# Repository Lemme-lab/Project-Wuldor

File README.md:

# Project Wuldor
---
## A completely custom 6 Axis Roboter-Arm (Still in progress) that won the 2022 HTL Mössingerstraße Technicus Award. 
---

---

---

---

---

---

---

---

---

## Features 
- Self Designed Stepper Motor Controller (A4988) 
- Self designed Main Controller with a small footprint
- Compact Size Factor
- Esthetic 
- Many other little Features

---

---

---

## Planned Code:
### General:  
A few bullet points and explanations for the code part. Different technologies and programming languages such as C++, WEB-Dev, and Flutter will be used. It will go from Basic C and register manipulation to UI-Development on Cross-Platform Mobile Apps.  
  
- Controlling Axis 1- 5  
- Save Control sequence  
- Remote  Connection  
- Desktop  Application  
- Website  
- Mobile App  
- PHP Database  
- C++, HTML, CSS, JS, FLUTTER, JAVA, Python
- Tensorflow, Keras

---
  
### Website:  
An HTML Website that must be functional and appealing to use. Features will be send via a ESP32 and the included Wireless module. Cross-platform Data will mean that we will have to save the current data and inputs on a small database. UI and other Features will mean that we have to use JS with or without an additional framework.  
 --- 

 --- 
- Checking Power Status  
- Check Wireless Connection  
- Current Voltage/Power Levels  
- Slider  Controlls for Motors  
- Test Motor func  
- Switch Mode (Normal Control, Train ,AI)  
- Cam Live Stream implementation  
- Stop/Start/hold -->pan> Slide buttons  
- Speed  
- Axis coordinates  
  
--- 
  
### Desktop Client  
A C++ or Java desktop client to be used when wired up to the robot arm. From the User ready interface to debbuging, testing and programming features will be included. This is one of the most important interface to the robot arm and as such it will be programmed first.  
  
- Checking Power Status  
- Check Wireless Connection  
- Current Voltage/Power Levels  
- Slider  Controlls for Motors  
- Test Motor func  
- Switch Mode (Normal Control,AI)  
- Cam  
- Debug Features / Console  
- Test  Features  
- Stop/Start/Hold -->  slidebuttons  
- Speed  
  
--- 
  
### Mobile Client  
Last we will do a Mobile Client app for controlling and checking the robot arm on the go. It will be programmed in Flutter or another Mobile Cross Platform Developer Kit.
--- 
  
---   
- Checking Power Status  
- Check Wireless Connection  
- Current-Voltage/Power Levels  
- Settings  
- Live Cam   

---

### Self-Test
Testclasses to exclude code-mistakes. Motors are working in the corract way and also the remote connection and controlling from the web applicatio, if so then we can put everything together and test the whole thing

- Motor
- Remote Connection
- Connections Seriell/Connectors 
  
---
### Currently in Work
---

---
The whole code will be versioned via GIT, inputs to the Roboter Arm tested, and the whole project will be publicly available on GitHub.
---
https://trello.com/b/jWCULnX8
---

## Stepper Motor + Reducer

---

---

------

## Stepper Motor Controller 

------

------

------

------

## Main Controller

------

------

------

------

## Roboter-Arm
---

---

---

---

---

---

------

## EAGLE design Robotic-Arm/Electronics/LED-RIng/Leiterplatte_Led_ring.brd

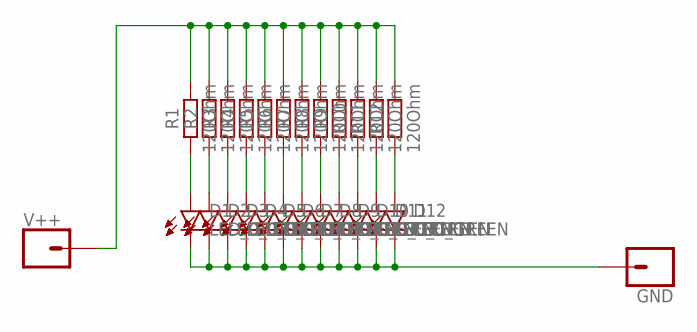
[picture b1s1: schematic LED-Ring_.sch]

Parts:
D1, D2, D3, D4, D5, D6, D7, D8, D9, D10, D11, D12: LED_GREEN; LEDC2012X105N_RND-R
GND: CONN_01PTH_2MM; 1X01_2MM
R1, R2, R3, R4, R5, R6, R7, R8, R9, R10, R11, R12: 120Ohm; RESC3216X70
V++: CONN_01PTH_2MM; 1X01_2MM

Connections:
unnamed: R1.2, R2.2, R3.2, R4.2, R5.2, R6.2, R7.2, R8.2, R9.2, R10.2, R11.2, R12.2, V++.1
unnamed: D1.A, R1.1
unnamed: D2.A, R2.1
unnamed: D3.A, R3.1
unnamed: D4.A, R4.1
unnamed: D5.A, R5.1
unnamed: D6.A, R6.1
unnamed: D7.A, R7.1
unnamed: D8.A, R8.1
unnamed: D9.A, R9.1
unnamed: D10.A, R10.1
unnamed: D11.A, R11.1
unnamed: D12.A, R12.1
unnamed: D1.C, D2.C, D3.C, D4.C, D5.C, D6.C, D7.C, D8.C, D9.C, D10.C, D11.C, D12.C, GND.1

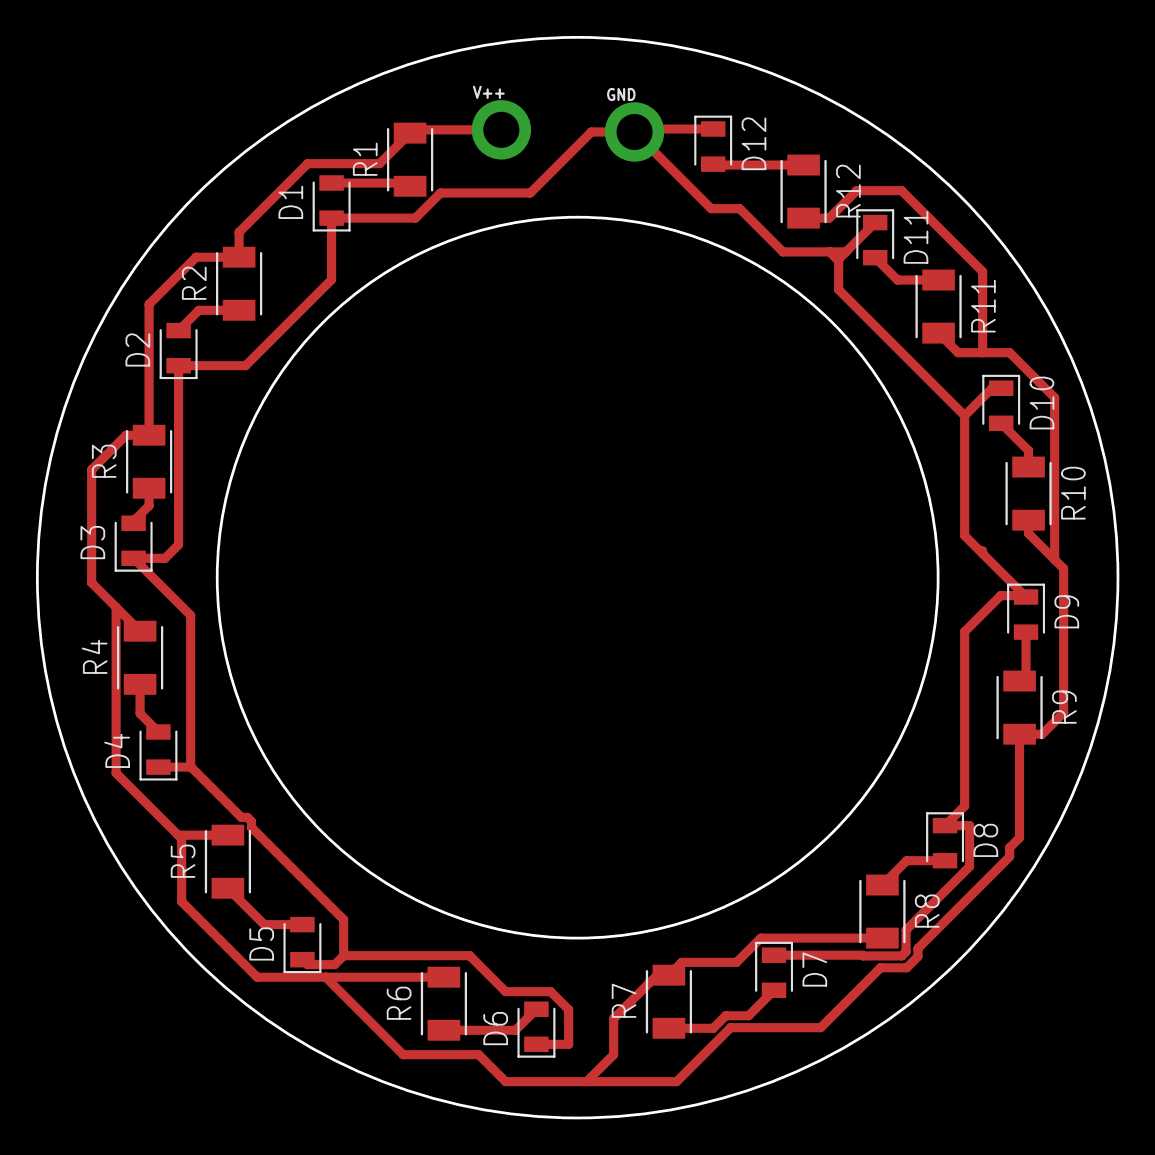
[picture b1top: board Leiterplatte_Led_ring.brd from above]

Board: 2 copper layers, 60.0 x 60.0 mm, 26 parts (0 on the bottom side), 14 nets.

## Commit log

2021-11-14 init
2022-01-16 Added Main Controller to Github
2022-01-16 Added Stepper Controller to Github
2022-01-21 Created and added 17HS15-1684S-HG100 100:1 Ratio High Torgue Stepper motor
2022-01-21 updatet 17HS4401
2022-01-21 Updatet Roboter Arm Combined
2022-01-21 Added Step_MD to Github
2022-01-22 Added Newest Version
    Renamed and added newest version
2022-01-22 Added 17HS15 Stepper Motor + Reducer
2022-01-23 ↓ Updatet ReadMe 3D-Model to new Version of Arm
2022-01-23 Added Code Overview
2022-01-25 Main Controller Routing New Alingment
2022-01-25 Updated ReadMe to new Versions of the Main Controller
2022-01-25 Updated Ground Polygon
2022-01-25 Updated ReadMe to new Silkscreen
2022-01-26 Updated ReadMe with Code Plans and Explanations
2022-01-26 Updated ReadMe to look better
2022-01-26 added Trello to ReadMe
2022-01-26 Added LICENSE to Main
2022-01-26 Update README.md
    Self-Test
2022-01-26 Update README.md
    KI
2022-01-28 Updated Main Controller
    Changed some parts on Seriell Interface
2022-01-28 Version 83 of Robot Arm
    Added Covers for the pulleys
2022-01-28 Added new and improved Renders for Version-83
2022-01-28 Added Improved Gerber Files for Manufacturing
2022-01-28 added new Motor renders and small changes to rm
2022-01-28 me stupid added wrong image
2022-01-29 Added V0.4 Main Controller improved Manufacturing Outputs
2022-01-29 Added V0.2 Motor Controller improved Manufacturing Outputs
2022-01-30 Added Price Lists
2022-01-30 Checked and updated Parts Chip shortage 2022
2022-01-30 Added Stepper Motor Price List
2022-01-30 Updated ReadMe to New Status Model/Electronics
2022-01-30 Added gif
2022-01-30 changed gif
2022-01-30 Better gif
2022-02-02 Added improved Main Controller 3D-Model
2022-02-02 Updated to Version 0. 94
2022-02-03 Added STLS for Manufacturing 3D-Models
2022-02-04 Updated Model to Version 0.107
2022-02-05 Added Nema 11 Stepper-Motor-Controller
2022-02-05 added real nema 17 controller
2022-02-05 Added Nema11 Motor-Controller Price List
2022-02-05 Added 11HS20-0674S-PG51 Stepper Motor
2022-02-05 Updated ReadMe to Version 0.116
2022-02-05 360 gif
2022-02-06 Updated ReadMe to Version 0.132
2022-02-06 Fixed ReadMe
2022-02-06 Added Version 0.132 Robotic-Arm
2022-02-08 Updated Motor Controller to Version 0.2.4
2022-02-19 Added/Updated Full Price List
2022-02-19 Added docx
2022-02-20 added version 0.150 Robot Arm
2022-02-22 updated to Version 0.152
2022-02-26 Changed Arm 4,5
2022-02-26 Added EoAT
2022-02-27 Updated to V1.0 Robot Arm Report
2022-02-28 Updated Docx
2022-03-01 added react environment
2022-03-01 changes on price list
2022-03-02 Added Web-HTML
2022-03-02 basic setup
2022-03-02 added tabs
2022-03-03 added styles to mode switch
2022-03-03 added js to switch mode
2022-03-03 margin
2022-03-03 small changes on mode changer
2022-03-03 status boxes
2022-03-03 button fix
2022-03-03 moved items from training to normal
2022-03-03 cam added
2022-03-03 base changed
2022-03-03 added power symbols
2022-03-03 Added Technical Drawings
2022-03-05 commit for git
2022-03-05 added js to status symbols
2022-03-05 added voltage and speed divs
2022-03-05 added pause/stop/start buttons
2022-03-05 added side buttons
2022-03-05 speed input changed
2022-03-07 added loader js
2022-03-07 small changes
2022-03-09 training under normal
2022-03-09 test
2022-03-09 training
2022-03-09 training upperboxes
2022-03-09 slide
2022-03-09 added coordinates slider
2022-03-09 added slider
2022-03-09 fixed style sheet
2022-03-09 modified slider
2022-03-09 added Training lower parts
2022-03-09 slider modified
2022-03-09 first three containers
2022-03-09 axis sliders ready
2022-03-10 myRange id modified
2022-03-10 fixed training
2022-03-10 slider values js
2022-03-10 js axis
2022-03-10 add remove buttons scaled
2022-03-10 added js to list
2022-03-10 added rest of js
2022-03-11 fixe issues on model
2022-03-11 change website style
2022-03-11 improved style
2022-03-11 added sleep image
2022-03-11 sleep style changed
2022-03-11 fixed bug
2022-03-11 fixed color
2022-03-12 price list
2022-03-12 changed gerbers and price list
2022-03-13 added mc coding environment
2022-03-13 added esp32 wireless features
2022-03-13 added sketches
2022-03-13 rework
2022-03-15 testing wireless esp32
2022-03-16 added main div
2022-03-16 sleep_main
2022-03-16 box -> sleep left + mid
2022-03-16 added right side of sleep side
2022-03-16 add something
2022-03-16 small changes on style
2022-03-16 fixe images and added links to right side sleep
2022-03-16 commit to pull
2022-03-16 add something new
2022-03-16 add something new to the new one
2022-03-16 sleep version 1.0
2022-03-16 fixed tab bug
2022-03-16 changed arm 4 and 5
2022-03-17 added query strings
2022-03-18 testing esp32 to website
2022-03-18 ahhhhh
2022-03-18 commit for test
2022-03-19 changed gerbers
2022-03-19 Update issue templates
2022-03-19 fixed arm 1 and 2
2022-03-20 panel gerber and base motor changed
2022-03-20 changed web server approach
2022-03-20 esp32 web client
2022-03-21 changed structure
2022-03-21 added motor programm
2022-03-21 for pull
2022-03-21 commit for pull
2022-03-21 bug fix
2022-03-21 bug fix v2
2022-03-22 fixed ne structure
2022-03-22 fixed web
2022-03-22 pcb updated
2022-03-22 small changes to main esp32 code
2022-03-22 implemented motor class
2022-03-23 small commit
2022-03-23 push for pull
2022-03-24 addded robotics libary
2022-03-24 covers updated
2022-03-26 removed rb libary
2022-03-26 added inverse kinematic test
2022-03-26 added rb libary
2022-03-27 changes to stls
2022-03-27 fixing inverse kinematics
2022-03-27 changes to code and models
2022-03-27 added base stand dxf
2022-03-28 changes to mc code
2022-03-29 fixed atmega code
2022-03-29 added pdf
2022-03-29 fixed merch
2022-03-29 fixed merge not "merch" ahhh
2022-03-30 added more features to atmega mc
2022-04-01 added info to main
2022-04-01 fixed some bugs
2022-04-02 Bump minimist from 1.2.5 to 1.2.6 in /Code/web
    Bumps [minimist](https://github.com/substack/minimist) from 1.2.5 to 1.2.6.
    - [Release notes](https://github.com/substack/minimist/releases)
    - [Commits](https://github.com/substack/minimist/compare/1.2.5...1.2.6)
    ---
    updated-dependencies:
    - dependency-name: minimist
2022-04-02 bug fixes and additions to atmega cpp
2022-04-02 small changes to atmega main cpp
2022-04-02 changes to atmega main
2022-04-03 added display code
2022-04-03 maybe fixed display code
2022-04-03 put web server into comments
2022-04-04 webserver 1.0
2022-04-04 changed display code
2022-04-04 fixed esp32 code structure
2022-04-04 fixed new structure
2022-04-04 webserver 1.1
2022-04-04 changes to webserver
2022-04-05 added terminal input code
2022-04-05 added buffer remover
2022-04-09 changes to eoat and front
2022-04-10 why did i start this project
2022-04-11 reworked code at atmega
2022-04-12 fixed motor drivers, added images, changed model
2022-04-12 Reworked Banner
2022-04-12 fixing banner and gif
2022-04-13 Added 4k Banner
2022-04-13 4k Banner
2022-04-15 webserver 1.4
2022-04-15 webserver 1.4.1
2022-04-15 renders, added SPI to ESP32
2022-04-16 added renders and logo
2022-04-17 fixed display code and modell
2022-04-18 removed display testing
2022-04-21 changes to esp32 main and webserver
2022-04-22 added eoat 2 test
2022-04-23 added preview of things in work
2022-04-24 changes to modell
2022-04-25 code structure
2022-04-26 changes to SPI
2022-05-02 changed 3d modell
2022-05-03 added Led Ring Code
2022-05-05 added Testing Feature add Coordinates
2022-05-15 added laser cutter files
2022-05-16 webserver final
2022-05-16 final web
2022-05-17 added setup for flutter (working in background)
2022-06-21 a lot of updates
2022-07-01 finall commit Won Technicus Award 2022
2022-07-01 Version 0.1 Project Wuldor
2022-09-23 added images
2022-09-23 Updated code
2022-09-23 fixed code writer
2022-09-23 fixed code author

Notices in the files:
parts and their libraries:
SparkFun-Connectors: Licensing: Creative Commons ShareAlike 4.0 International - https://creativecommons.org/licenses/by-sa/4.0
